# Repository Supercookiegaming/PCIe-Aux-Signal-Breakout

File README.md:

# PCIe Auxiliary Signal Breakout Card

## Overview
The PCIe Auxiliary Signal Breakout Card is designed to make the auxiliary signals in a PCIe connection available to the user. This includes SMBus and JTAG. The card also provides 12V, 5V and 3.3V power and the PCIe reset signal which also functions as a 3.3V and 12V power good signal.

## Specifications

* 10W Total Power Output
    * Up to 3.0A on 3.3V
    * Up to 1.0A on 5V (optional)
    * Up to 0.5A on 12V
    * Up to 0.375A on 3.3V Aux
* Open-Drain SMBus
    * 3.3V Signal Levels
* IEEE Standard 1149.1 JTAG
    * 3.3V Signal Levels
* Always on 3.3V Aux rail
* Standard and Low Profile Brackets included

## Pinout

## Instructions

* [Ordering Instructions](Instructions/PCB_Order_Instructions.md)
* [KiCad Instructions](Instructions/KiCad_Install_Instructions.md)
* [Soldering Instructions](Instructions/Soldering_Instructions.md)
* [3D Printing Instructions](3D-Printing)
  
## Issues and Feature Requests

| Issue/Feature | Issue Number | Status | Version Milestone |
|-------|--------|--------|--------|

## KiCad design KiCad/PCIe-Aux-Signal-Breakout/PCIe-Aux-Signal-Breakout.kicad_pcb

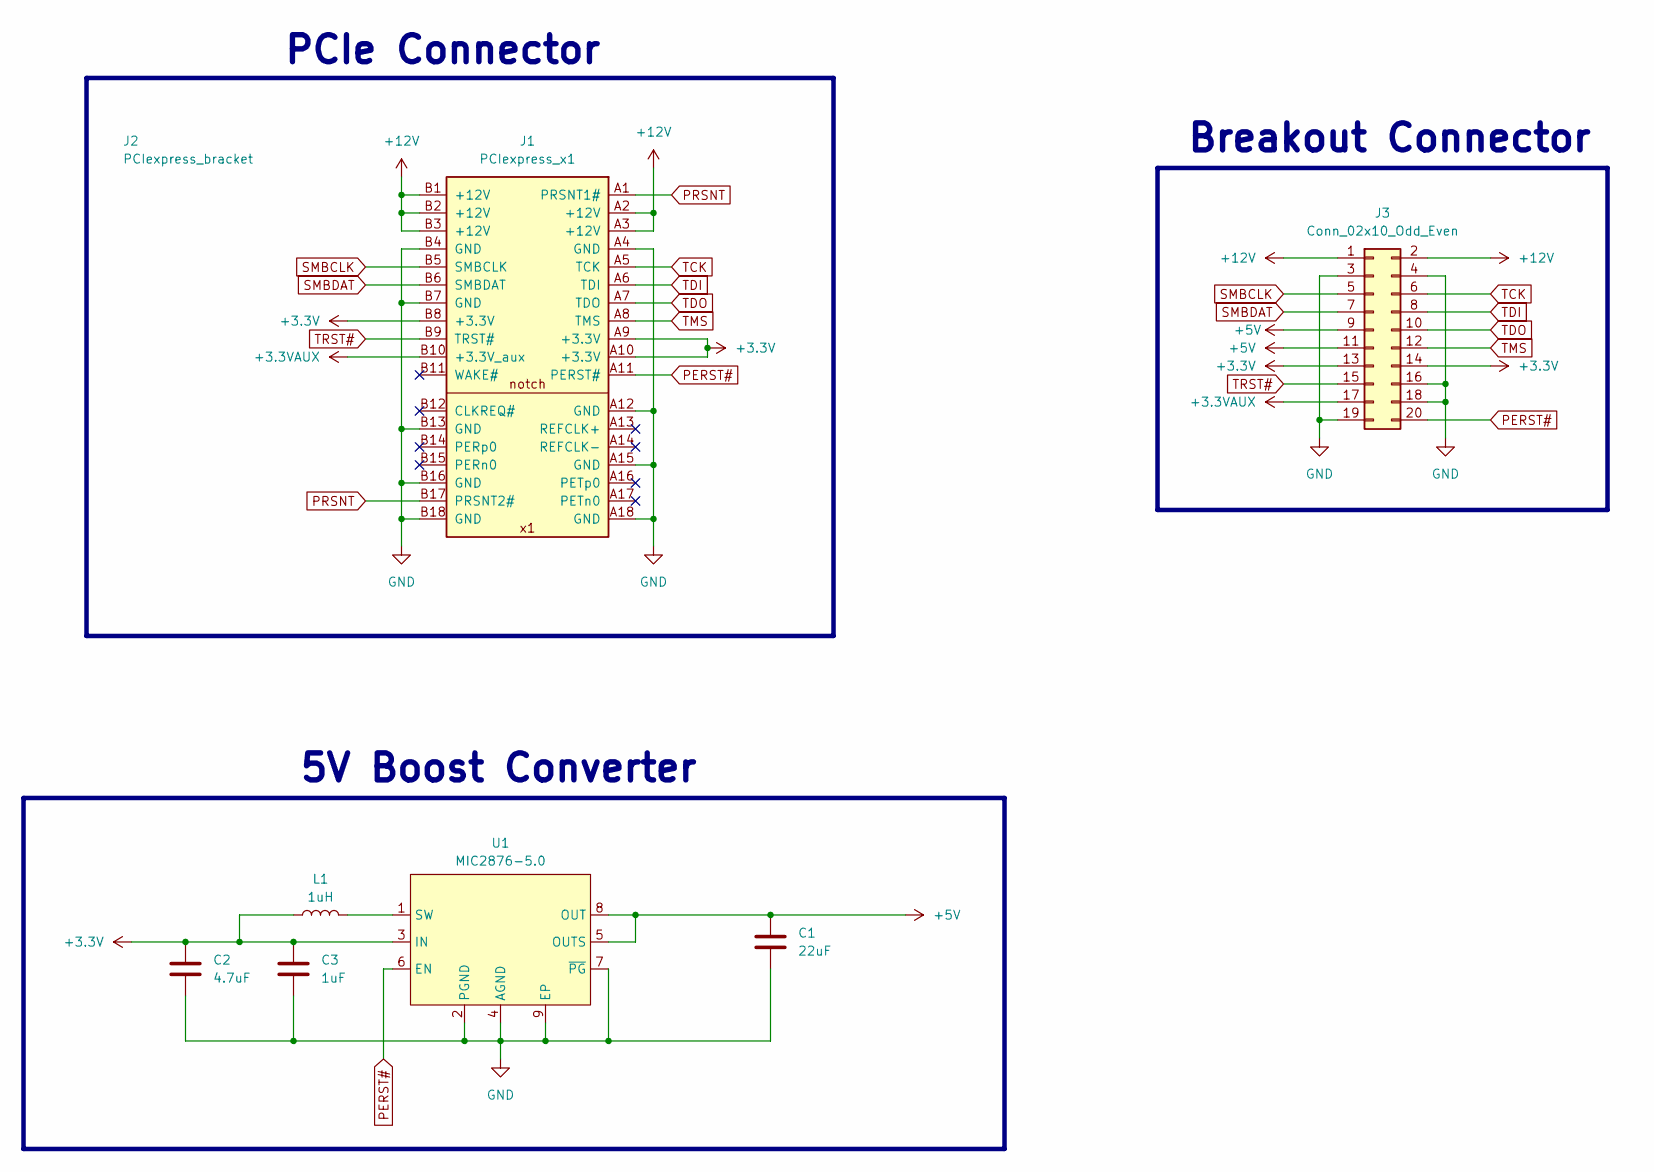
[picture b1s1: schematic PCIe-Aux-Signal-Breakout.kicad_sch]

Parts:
C1: 22uF; C_0805_2012Metric
C2: 4.7uF; C_0603_1608Metric
C3: 1uF; C_0603_1608Metric
J1: PCIexpress_x1
J2: PCIexpress_bracket; PCIexpress_bracket_low
J3: Conn_02x10_Odd_Even; IDC-Header_2x10_P2.54mm_Horizontal
L1: 1uH; L_2520_INPAQ
U1: MIC2876-5.0; 8-Lead UDFN

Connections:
+3.3V: C2.1, C3.1, J1.A9 (+3.3V), J1.A10 (+3.3V), J1.B8 (+3.3V), J3.13, J3.14, L1.1, U1.3 (IN)
+3.3VAUX: J1.B10 (+3.3V_aux), J3.17
+5V: C1.1, J3.9, J3.11, U1.5 (OUTS), U1.8 (OUT)
+12V: J1.A2 (+12V), J1.A3 (+12V), J1.B1 (+12V), J1.B2 (+12V), J1.B3 (+12V), J3.1, J3.2
GND: C1.2, C2.2, C3.2, J1.A4 (GND), J1.A12 (GND), J1.A15 (GND), J1.A18 (GND), J1.B4 (GND), J1.B7 (GND), J1.B13 (GND), J1.B16 (GND), J1.B18 (GND), J3.3, J3.4, J3.16, J3.18, J3.19, U1.2 (PGND), U1.4 (AGND), U1.7 (~PG), U1.9 (EP)
unnamed: L1.2, U1.1 (SW)
PERST#: J1.A11 (PERST#), J3.20, U1.6 (EN)
PRSNT: J1.A1 (PRSNT1#), J1.B17 (PRSNT2#)
SMBCLK: J1.B5 (SMBCLK), J3.5
SMBDAT: J1.B6 (SMBDAT), J3.7
TCK: J1.A5 (TCK), J3.6
TDI: J1.A6 (TDI), J3.8
TDO: J1.A7 (TDO), J3.10
TMS: J1.A8 (TMS), J3.12
TRST#: J1.B9 (TRST#), J3.15

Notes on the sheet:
5V Boost Converter
Breakout Connector
PCIe Connector

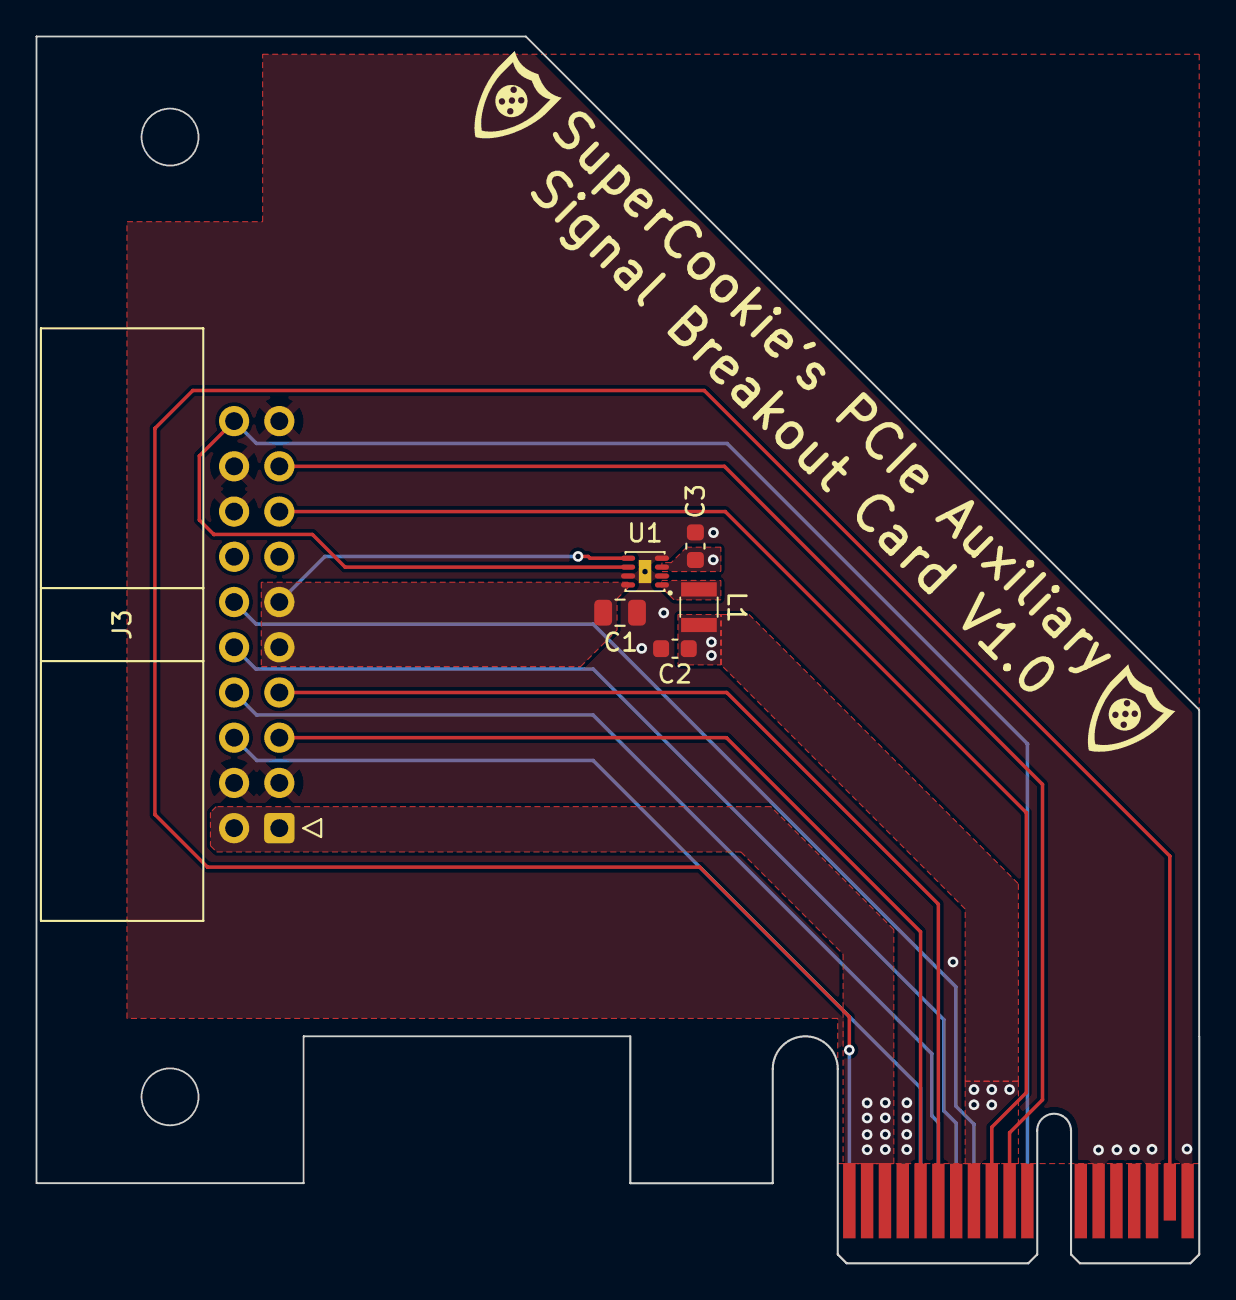
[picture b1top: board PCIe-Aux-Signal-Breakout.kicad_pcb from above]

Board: 2 copper layers, 65.3 x 68.9 mm, 8 parts (0 on the bottom side), 15 nets.

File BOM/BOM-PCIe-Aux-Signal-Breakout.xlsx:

Board QTY | 1
Total Price | 1.6100000000000003
Board Designator | Part Number | Part Purpose | QTY per Board | Unit Price | QTY Needed | Total Price | Link
J3 | BHR-20-HUA | Singal Breakout Header | 1 | 0.61 | 1 | 0.61 | https://www.digikey.com/en/products/detail/adam-tech/BHR-20-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
U1 | MIC2876-5.0YMT-TR | 5V Boost Converter | 1 | 0.62 | 1 | 0.62 | https://www.digikey.com/en/products/detail/microchip-technol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
L1 | WIP252012S-1R0MLDG | 1uH Boost Converter Inductor | 1 | 0.1 | 1 | 0.1 | https://www.digikey.com/en/products/detail/inpaq-technology-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
C1 | CL21A226MQQNNNE | 22uF 5V Boost Converter Output Cap | 1 | 0.12 | 1 | 0.12 | https://www.digikey.com/en/products/detail/samsung-electro-m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
C2 | CL10A475KP8NNNC | 4.7uF 5V Boost Converter Input Cap | 1 | 0.08 | 1 | 0.08 | https://www.digikey.com/en/products/detail/samsung-electro-m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
C3 | CL10B105KP8NNNC | 1uF 5V Boost Converter Input Cap | 1 | 0.08 | 1 | 0.08 | https://www.digikey.com/en/products/detail/samsung-electro-m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

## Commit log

2025-08-08 Created KiCad Files
    created kicad project
    added project kicad library
    added gitignore file
2025-08-09 started pcb design
2025-08-09 finished v1.0 design
    finished v1.0 pcb
    added low and standard profile pcie bracket with custom connector cutout
    made gerber files
    added instruction files
    added images of the board
    added BOM
2025-08-09 added drill files to gerber
2025-08-09 updated name to be markdown relative path compatible
2025-08-09 Added Schematic and 3D printing files
    -updated board silkscreen
    -added STL files for pcie brackets
    -added 3d model folder for assembled boards
